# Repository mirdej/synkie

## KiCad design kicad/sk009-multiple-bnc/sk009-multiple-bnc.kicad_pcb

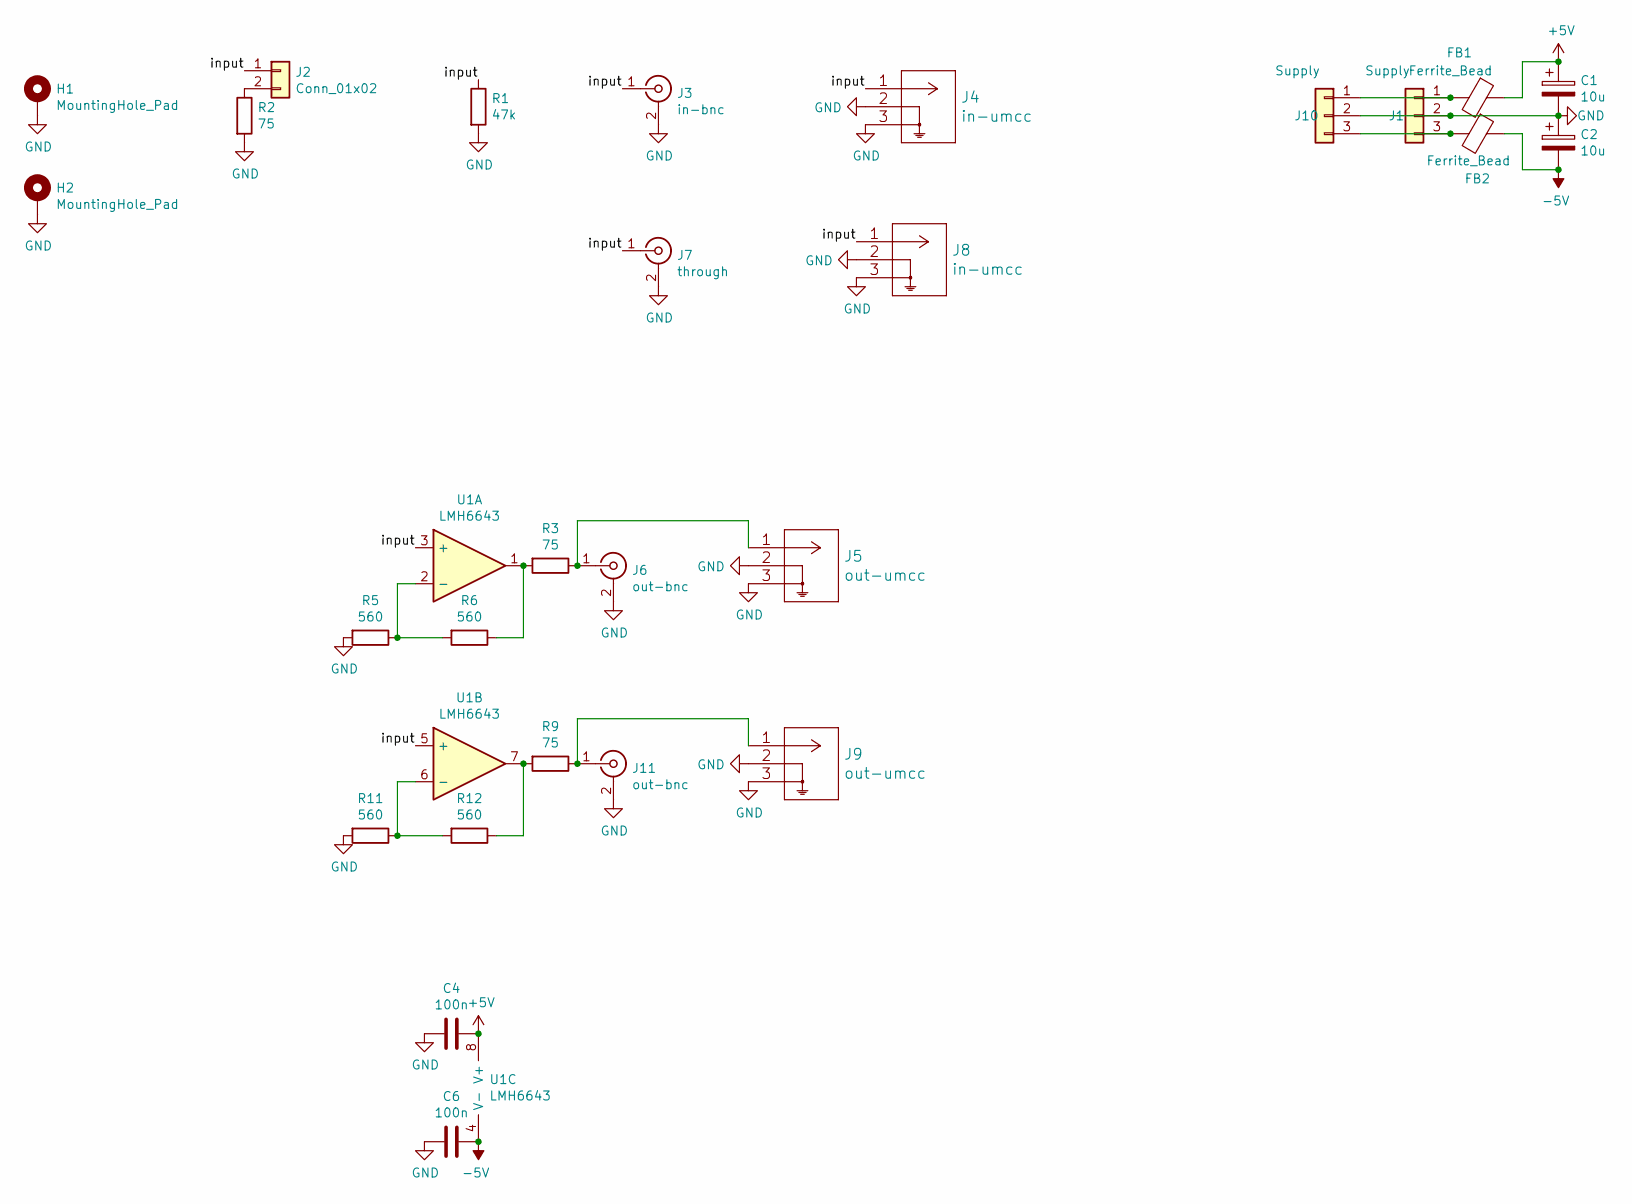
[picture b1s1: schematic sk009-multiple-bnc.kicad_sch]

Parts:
C1, C2: 10u; C_0805_2012Metric; LCSC C15850
C4, C6: 100n; C_0603_1608Metric; LCSC C14663
FB1, FB2: Ferrite_Bead; L_0805_2012Metric; LCSC C1017
H1, H2: MountingHole_Pad; MountingHole_3.2mm_M3_DIN965_Pad
J1, J10: Supply; Molex_KK-254_AE-6410-03A_1x03_P2.54mm_Vertical
J2: Conn_01x02; PinHeader_1x02_P2.54mm_Vertical
J3: in-bnc; BNC_Aliexpress
J4, J8: in-umcc; TE_UMCC_2337019-1
J5, J9: out-umcc; TE_UMCC_2337019-1
J6, J11: out-bnc; BNC_Aliexpress
J7: through; BNC_Aliexpress
R1: 47k; R_0603_1608Metric; LCSC C25819
R2, R3, R9: 75; R_0603_1608Metric; LCSC C4275
R5, R6, R11, R12: 560; R_0603_1608Metric; LCSC C23204
U1: LMH6643; VSSOP-8_3x3mm_P0.65mm; LCSC C478382

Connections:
+5V: C1.1, C4.1, FB1.1, U1.8 (V+)
-5V: C2.2, C6.1, FB2.1, U1.4 (V-)
/input: J2.1, J3.1 (In), J4.1, J7.1 (In), J8.1, R1.1, U1.3 (+), U1.5 (+)
GND: C1.2, C2.1, C4.2, C6.2, H1.1 (1_1), H2.1 (1_1), J1.2, J3.2 (Ext), J4.2, J4.3, J5.2, J5.3, J6.2 (Ext), J7.2 (Ext), J8.2, J8.3, J9.2, J9.3, J10.2, J11.2 (Ext), R1.2, R2.2, R5.2, R11.2
unnamed: FB1.2, J1.1, J10.1
unnamed: FB2.2, J1.3, J10.3
unnamed: J2.2, R2.1
unnamed: J5.1, J6.1 (In), R3.1
unnamed: J9.1, J11.1 (In), R9.1
unnamed: R3.2, R6.1, U1.1
unnamed: R9.2, R12.1, U1.7
unnamed: R5.1, R6.2, U1.2 (-)
unnamed: R11.1, R12.2, U1.6 (-)

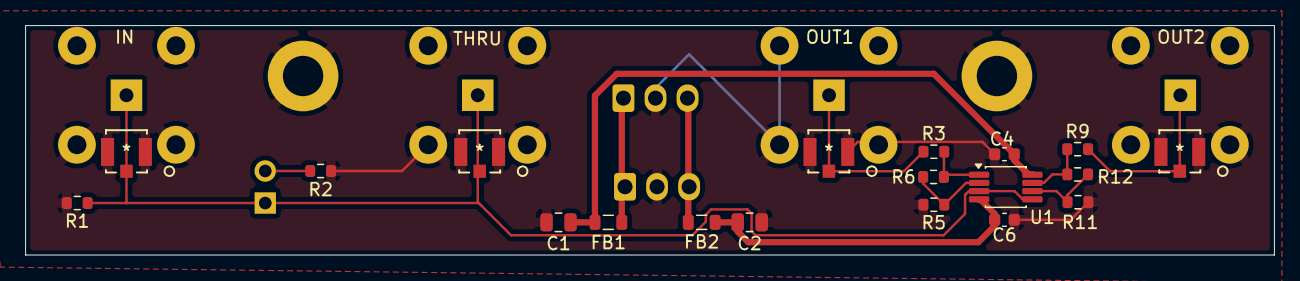
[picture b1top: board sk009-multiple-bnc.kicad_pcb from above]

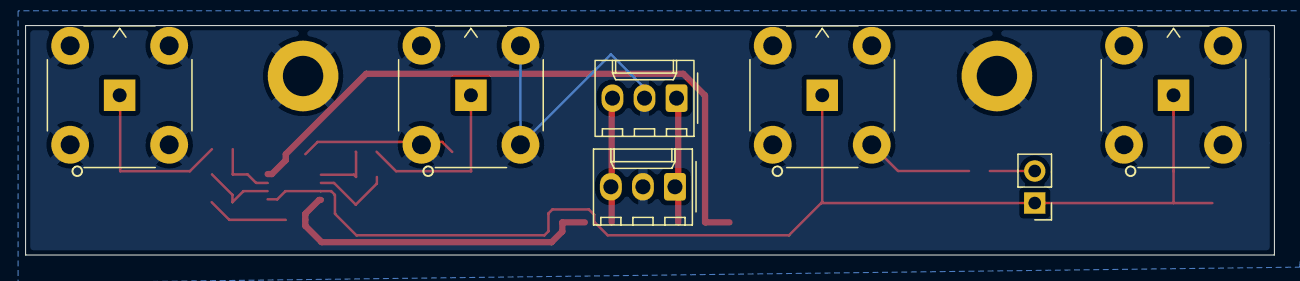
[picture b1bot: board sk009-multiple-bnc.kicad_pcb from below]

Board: 2 copper layers, 99.0 x 18.2 mm, 28 parts (7 on the bottom side), 13 nets.

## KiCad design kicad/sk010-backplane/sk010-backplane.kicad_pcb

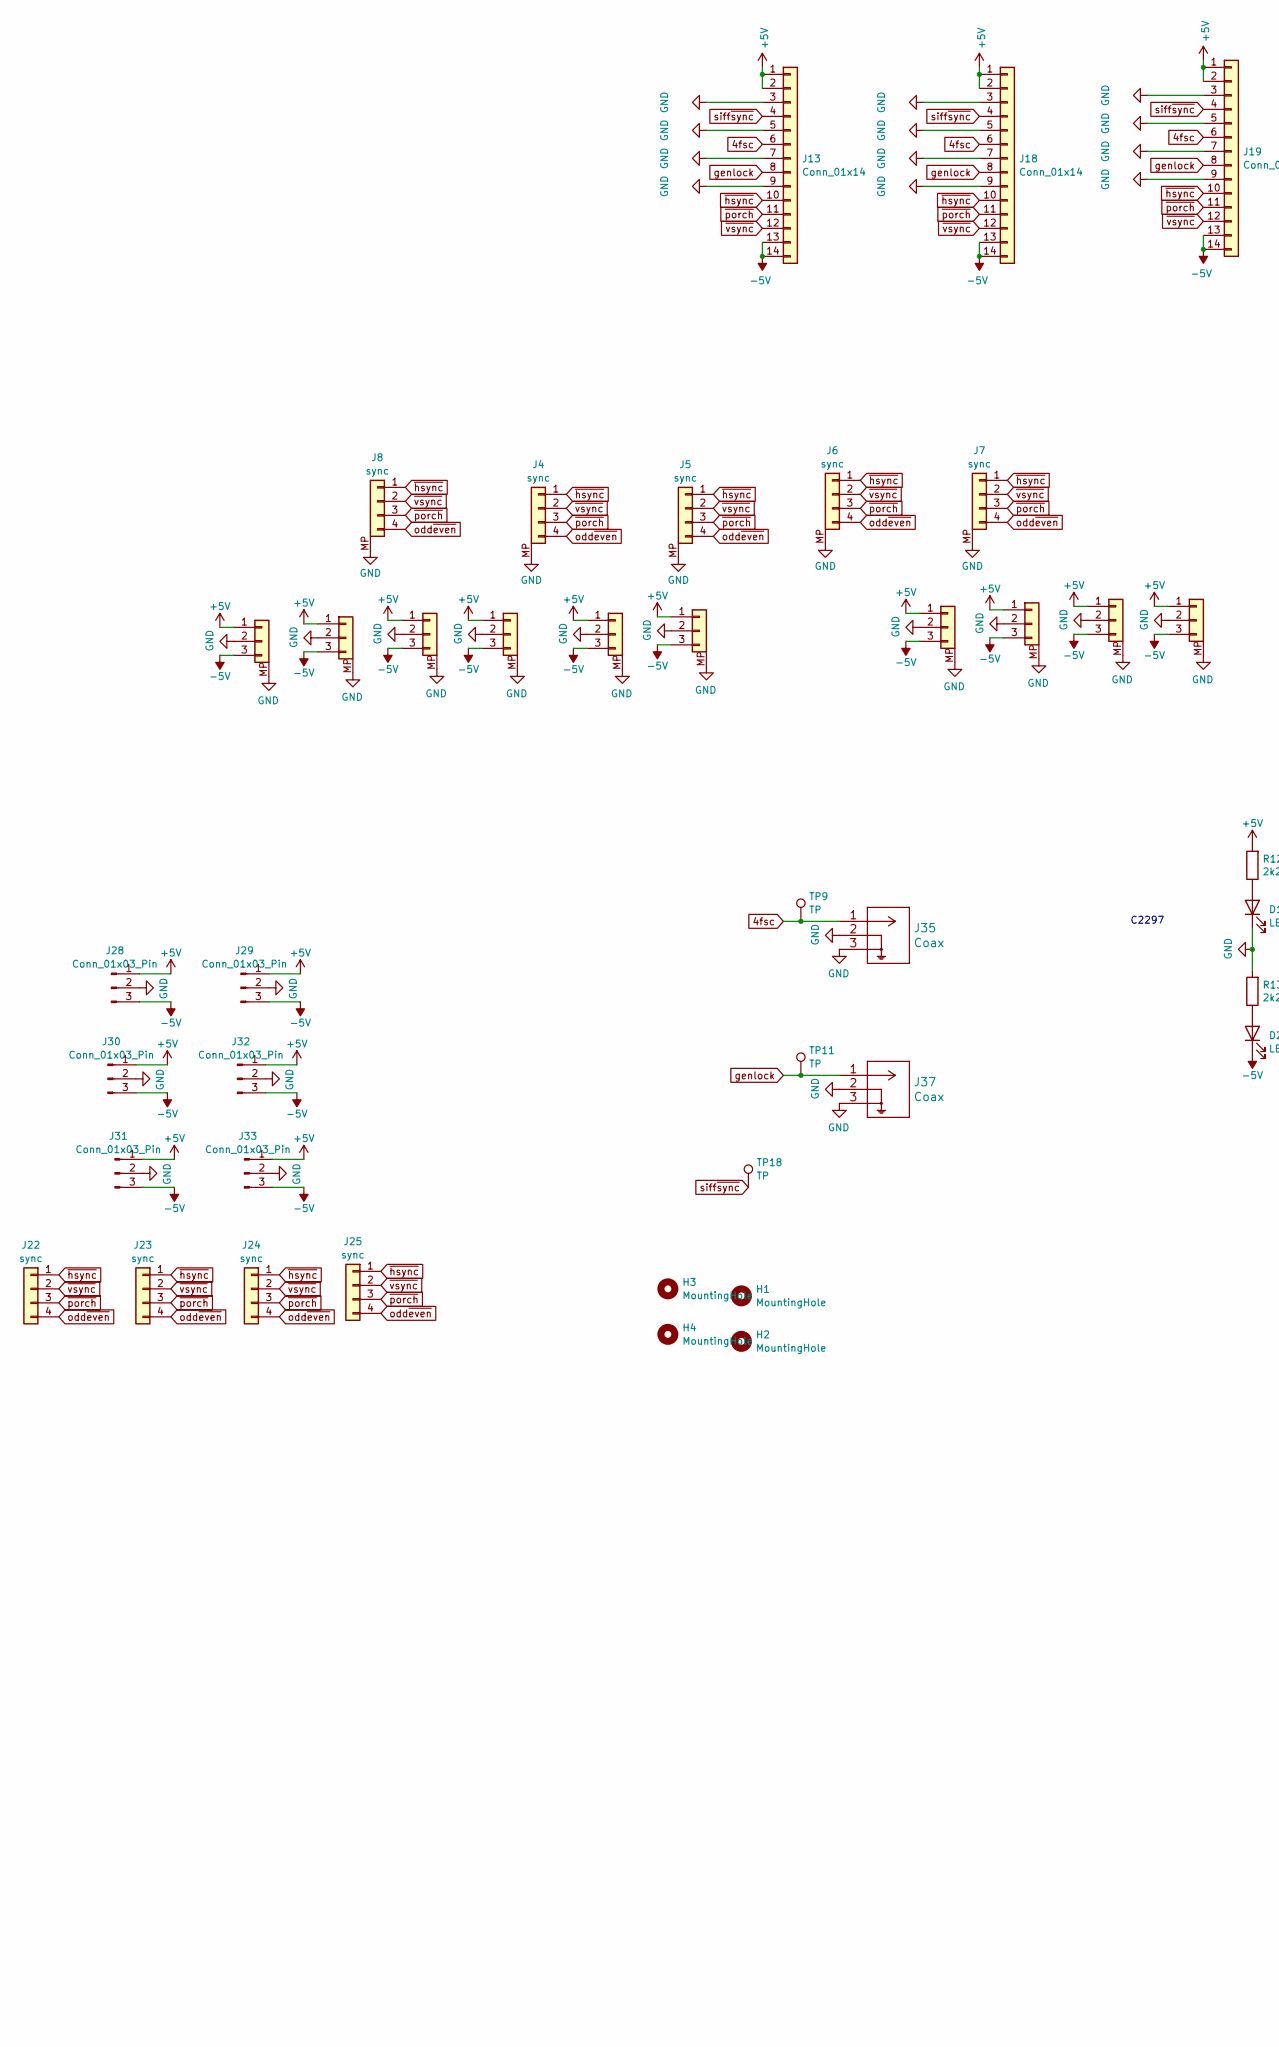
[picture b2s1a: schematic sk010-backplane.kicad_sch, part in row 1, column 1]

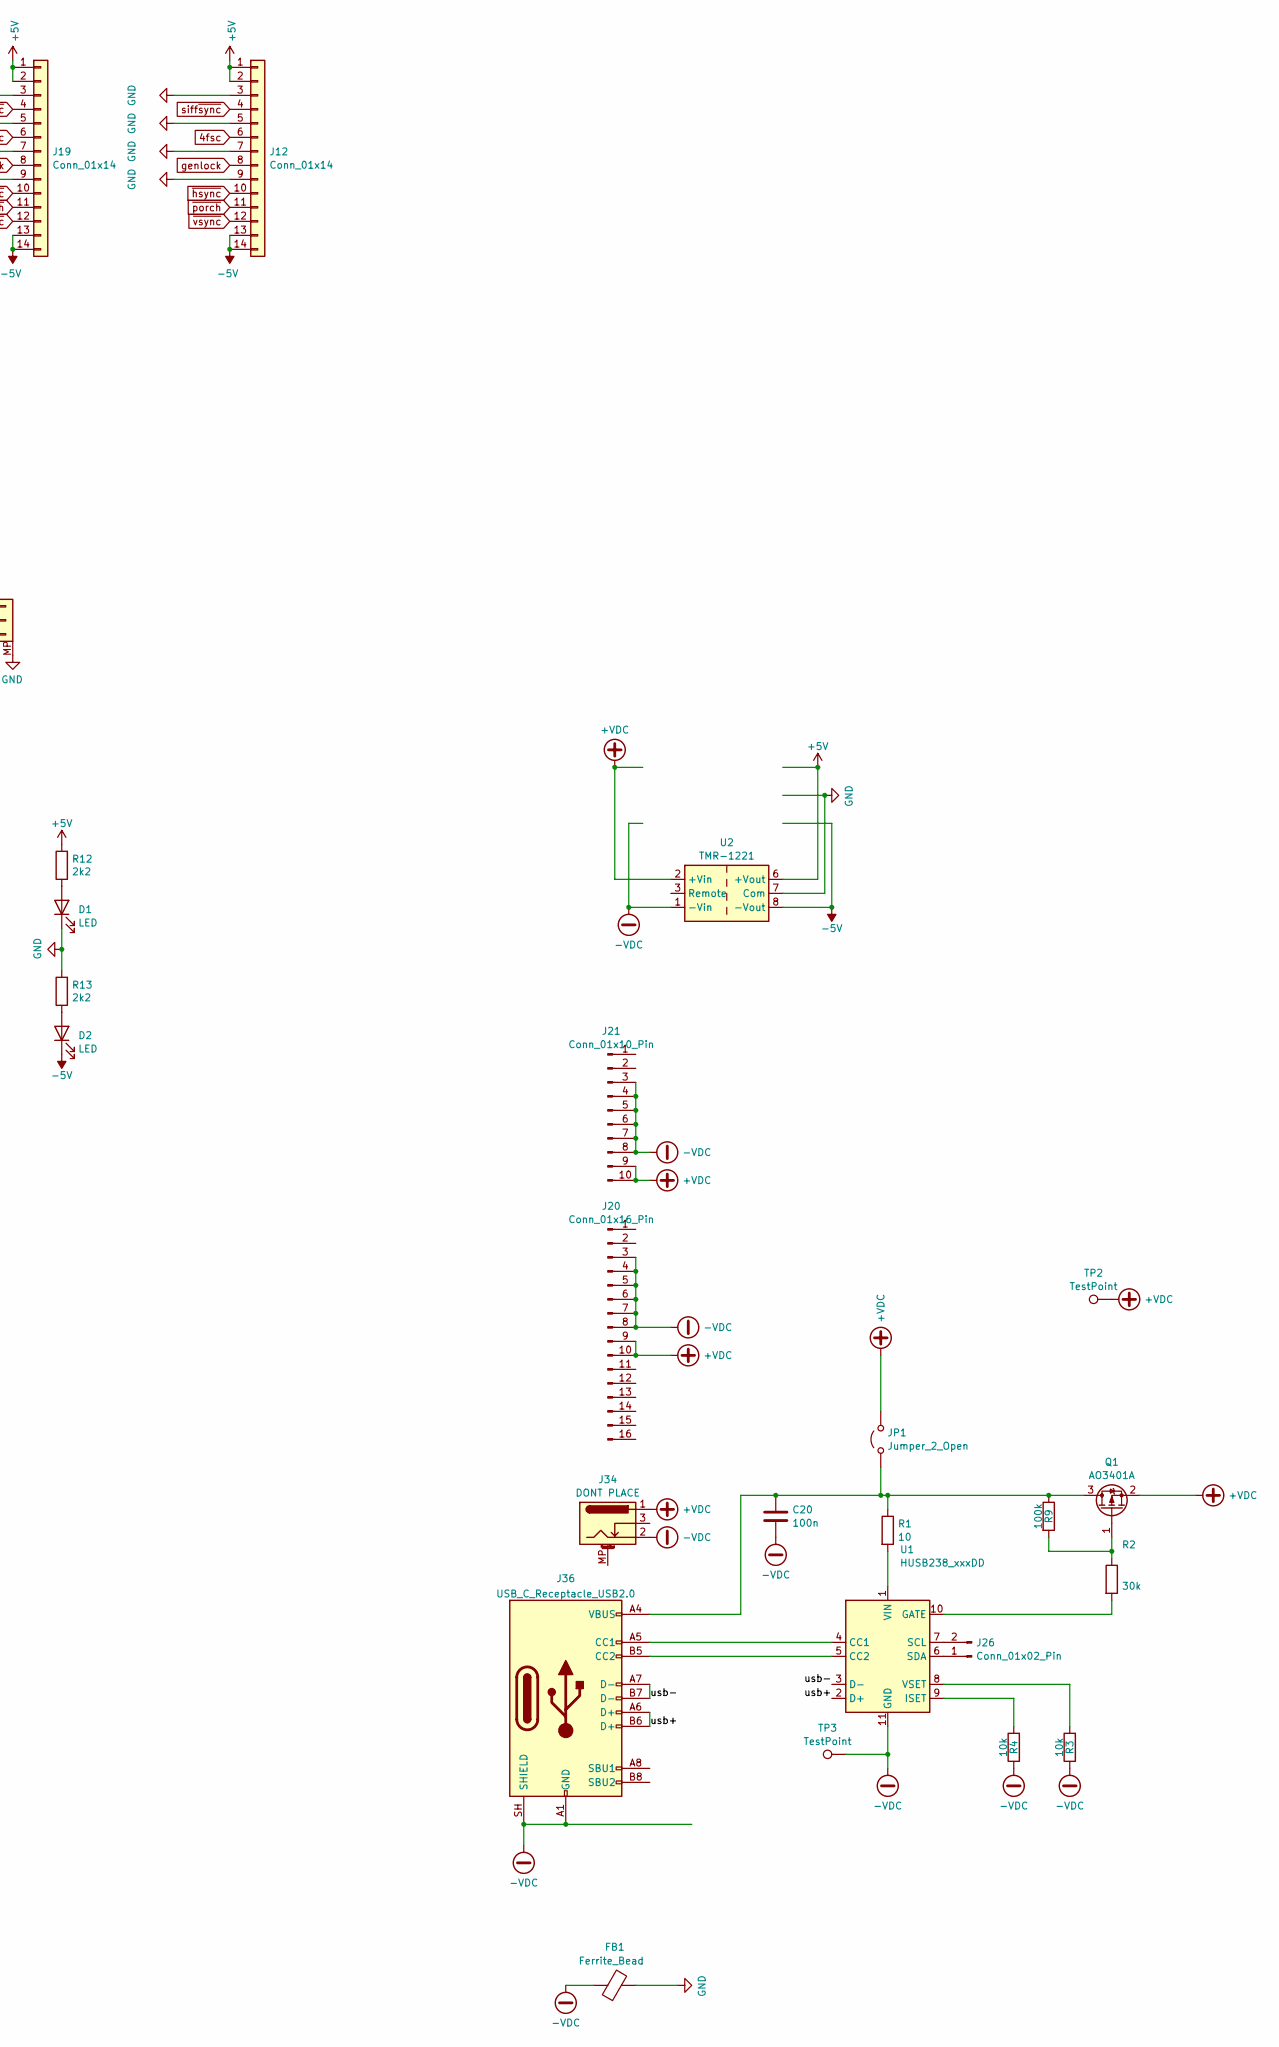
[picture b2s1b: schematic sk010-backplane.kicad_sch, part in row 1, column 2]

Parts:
C20: 100n; C_0603_1608Metric; LCSC C14663
D1, D2: LED; LED_0805_2012Metric; LCSC C2297
FB1: Ferrite_Bead; L_0805_2012Metric_Pad1.15x1.40mm_HandSolder; LCSC C1017
H1, H2, H3, H4: MountingHole; MountingHole_3.2mm_M3_DIN965
J1, J2, J3, J9, J10, J11, J14, J15, J16, J17: Conn_01x03; Molex_PicoBlade_53398-0371_1x03-1MP_P1.25mm_Vertical; LCSC C293633
J4, J5, J6, J7, J8: sync; Molex_PicoBlade_53398-0471_1x04-1MP_P1.25mm_Vertical
J12, J13, J18, J19: Conn_01x14; IDC-Header_2x07_P2.54mm_Vertical
J20: Conn_01x16_Pin; IDC-Header_2x08_P2.54mm_Vertical
J21: Conn_01x10_Pin; IDC-Header_2x05_P2.54mm_Vertical
J22, J23, J24, J25: sync; Molex_KK-254_AE-6410-04A_1x04_P2.54mm_Vertical; LCSC C17617036
J26: Conn_01x02_Pin; smd-2pin
J28, J29, J30, J31, J32, J33: Conn_01x03_Pin; Molex_KK-254_AE-6410-03A_1x03_P2.54mm_Vertical
J34: DONT PLACE; BarrelJack_CUI_PJ-079BH_Horizontal
J35, J37: Coax; TE_UMCC_2337019-1; LCSC C5137195
J36: USB_C_Receptacle_USB2.0; USB_C_Receptacle_HRO_TYPE-C-31-M-12; LCSC C165948
JP1: Jumper_2_Open; SolderJumper-2_P1.3mm_Open_Pad1.0x1.5mm
Q1: AO3401A; SOT-23; LCSC C15127
R1: 10; R_0603_1608Metric; LCSC C22859
R2: 30k; R_0603_1608Metric; LCSC C22984
R3, R4: 10k; R_0603_1608Metric; LCSC C25804
R9: 100k; R_0603_1608Metric; LCSC C25803
R12, R13: 2k2; R_0603_1608Metric; LCSC C4190
TP2, TP3: TestPoint; TestPoint_THTPad_D4.0mm_Drill2.0mm
TP9, TP11, TP18: TP; TestPoint_THTPad_D4.0mm_Drill2.0mm
U1: HUSB238_xxxDD; WDFN-10-1EP_3x3mm_P0.5mm_EP1.8x2.5mm; LCSC C7471904
U2: TMR-1221; Converter_DCDC_TRACO_TEC2-12xxWI_24xxWI_48xxWI_THT

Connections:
4fsc: J12.6, J13.6, J18.6, J19.6, J35.1, TP9.1 (1_1)
+5V: J1.1, J2.1, J3.1, J9.1, J10.1, J11.1, J12.1, J12.2, J13.1, J13.2, J14.1, J15.1, J16.1, J17.1, J18.1, J18.2, J19.1, J19.2, J28.1, J29.1, J30.1, J31.1, J32.1, J33.1, R12.2, U2.6 (+Vout)
+VDC: J20.9, J20.10, J21.9, J21.10, J34.1, JP1.2 (B), Q1.2 (S), TP2.1 (1_1), U2.2 (+Vin)
-5V: D2.1 (K), J1.3, J2.3, J3.3, J9.3, J10.3, J11.3, J12.13, J12.14, J13.13, J13.14, J14.3, J15.3, J16.3, J17.3, J18.13, J18.14, J19.13, J19.14, J28.3, J29.3, J30.3, J31.3, J32.3, J33.3, U2.8 (-Vout)
-VDC: C20.1, FB1.1, J20.3, J20.4, J20.5, J20.6, J20.7, J20.8, J21.3, J21.4, J21.5, J21.6, J21.7, J21.8, J34.2, J36.A1 (GND), J36.A12 (GND), J36.B1 (GND), J36.B12 (GND), J36.SH (SHIELD), R3.1, R4.1, TP3.1 (1_1), U1.11 (GND), U2.1 (-Vin)
/usb+: J36.A6 (D+), J36.B6 (D+), U1.2 (D+)
/usb-: J36.A7 (D-), J36.B7 (D-), U1.3 (D-)
GND: D1.1 (K), FB1.2, J1.2, J1.MP, J2.2, J2.MP, J3.2, J3.MP, J4.MP, J5.MP, J6.MP, J7.MP, J8.MP, J9.2, J9.MP, J10.2, J10.MP, J11.2, J11.MP, J12.3, J12.5, J12.7, J12.9, J13.3, J13.5, J13.7, J13.9, J14.2, J14.MP, J15.2, J15.MP, J16.2, J16.MP, J17.2, J17.MP, J18.3, J18.5, J18.7, J18.9, J19.3, J19.5, J19.7, J19.9, J28.2, J29.2, J30.2, J31.2, J32.2, J33.2, J35.2, J35.3, J37.2, J37.3, R13.2, U2.7 (Com)
unnamed: D1.2 (A), R12.1
unnamed: D2.2 (A), R13.1
unnamed: J26.1, U1.6 (SDA)
unnamed: J26.2, U1.7 (SCL)
unnamed: J36.A5 (CC1), U1.4 (CC1)
unnamed: J36.B5 (CC2), U1.5 (CC2)
unnamed: C20.2, J36.A4 (VBUS), J36.A9 (VBUS), J36.B4 (VBUS), J36.B9 (VBUS), JP1.1 (A), Q1.3 (D), R1.1, R9.1
unnamed: Q1.1 (G), R2.1, R9.2
unnamed: R2.2, U1.10 (GATE)
unnamed: R4.2, U1.9 (ISET)
unnamed: R1.2, U1.1 (VIN)
unnamed: R3.2, U1.8 (VSET)
genlock: J12.8, J13.8, J18.8, J19.8, J37.1, TP11.1 (1_1)
odd~even: J4.4, J5.4, J6.4, J7.4, J8.4, J22.4, J23.4, J24.4, J25.4
siff~sync: J12.4, J13.4, J18.4, J19.4, TP18.1 (1_1)
~hsync: J4.1, J5.1, J6.1, J7.1, J8.1, J12.10, J13.10, J18.10, J19.10, J22.1, J23.1, J24.1, J25.1
~porch: J4.3, J5.3, J6.3, J7.3, J8.3, J12.11, J13.11, J18.11, J19.11, J22.3, J23.3, J24.3, J25.3
~vsync: J4.2, J5.2, J6.2, J7.2, J8.2, J12.12, J13.12, J18.12, J19.12, J22.2, J23.2, J24.2, J25.2

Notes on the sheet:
C2297

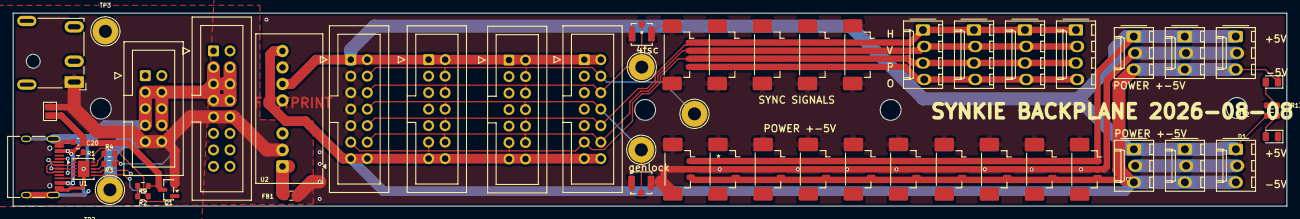
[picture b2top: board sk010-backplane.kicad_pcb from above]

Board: 2 copper layers, 196.1 x 29.7 mm, 60 parts (1 on the bottom side), 26 nets.

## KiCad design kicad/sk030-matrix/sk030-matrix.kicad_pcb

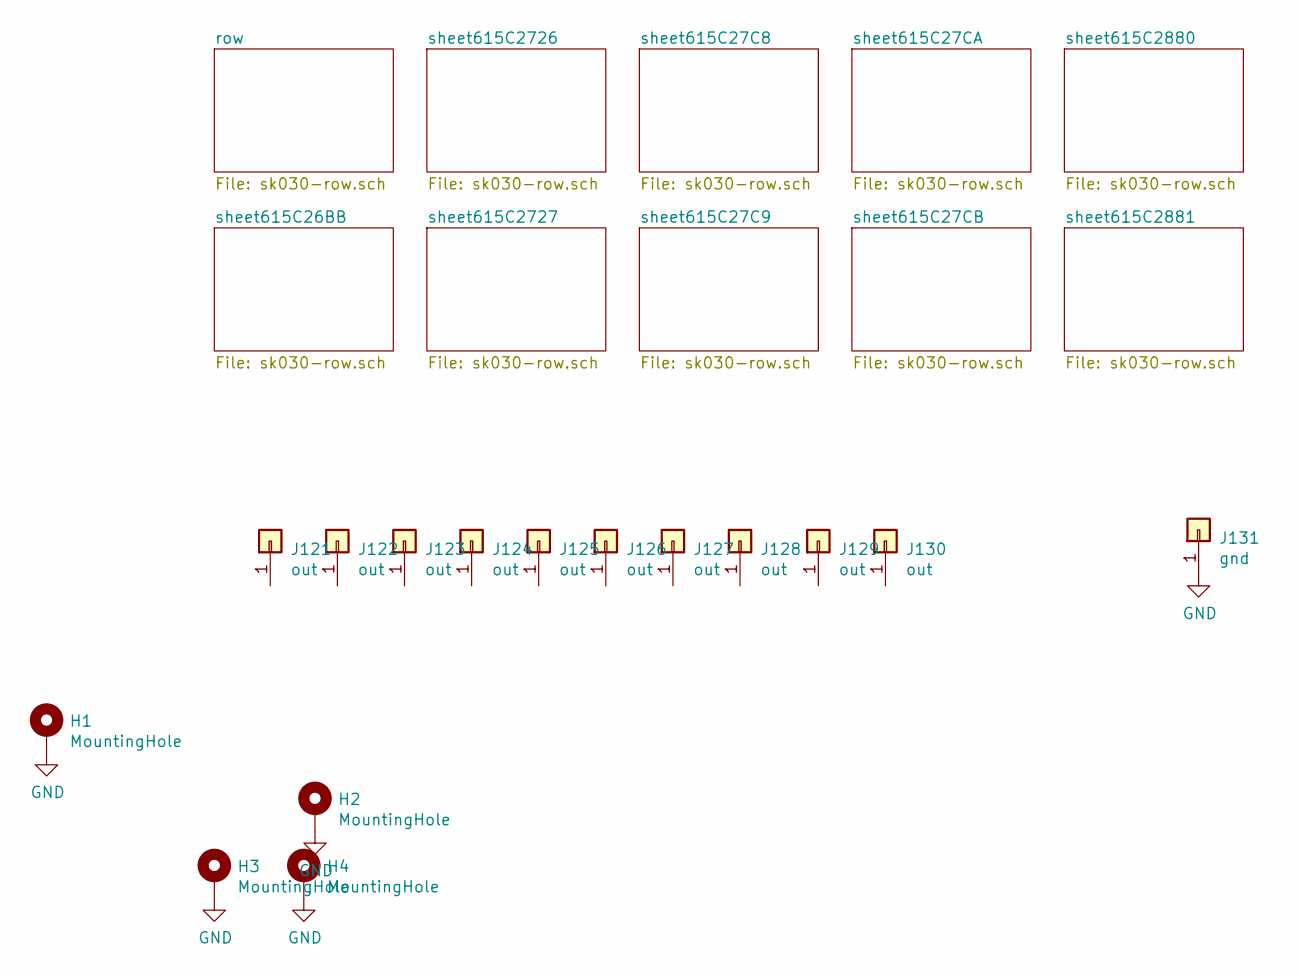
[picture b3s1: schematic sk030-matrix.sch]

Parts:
H1, H2, H3, H4: MountingHole; MountingHole_2.7mm_M2.5
J121, J122, J123, J124, J125, J126, J127, J128, J129, J130: out; Matrixpad
J131: gnd; smd-1pin

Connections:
GND: H1.1, H2.1, H3.1, H4.1, J131.1

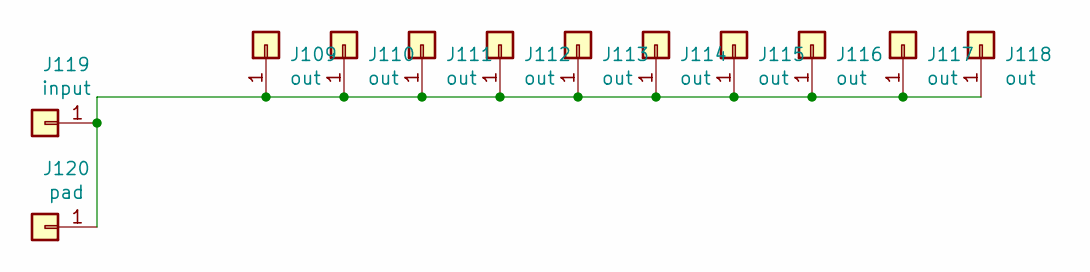
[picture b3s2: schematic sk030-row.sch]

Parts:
J1, J2, J3, J4, J5, J6, J7, J8, J9, J10: out; Matrixpad
J11: input; Matrixpad
J12: pad; smd-1pin

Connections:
unnamed: J1.1, J2.1, J3.1, J4.1, J5.1, J6.1, J7.1, J8.1, J9.1, J10.1, J11.1, J12.1

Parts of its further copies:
J13, J14, J15, J16, J17, J18, J19, J20, J21, J22, J25, J26, J27, J28, J29, J30, J31, J32, J33, J34, J37, J38, J39, J40, J41, J42, J43, J44, J45, J46, J49, J50, J51, J52, J53, J54, J55, J56, J57, J58, J61, J62, J63, J64, J65, J66, J67, J68, J69, J70, J73, J74, J75, J76, J77, J78, J79, J80, J81, J82, J85, J86, J87, J88, J89, J90, J91, J92, J93, J94, J97, J98, J99, J100, J101, J102, J103, J104, J105, J106, J109, J110, J111, J112, J113, J114, J115, J116, J117, J118: out; Matrixpad
J23, J35, J47, J59, J71, J83, J95, J107, J119: input; Matrixpad
J24, J36, J48, J60, J72, J84, J96, J108, J120: pad; smd-1pin

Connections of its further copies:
unnamed: J13.1, J14.1, J15.1, J16.1, J17.1, J18.1, J19.1, J20.1, J21.1, J22.1, J23.1, J24.1
unnamed: J25.1, J26.1, J27.1, J28.1, J29.1, J30.1, J31.1, J32.1, J33.1, J34.1, J35.1, J36.1
unnamed: J37.1, J38.1, J39.1, J40.1, J41.1, J42.1, J43.1, J44.1, J45.1, J46.1, J47.1, J48.1
unnamed: J49.1, J50.1, J51.1, J52.1, J53.1, J54.1, J55.1, J56.1, J57.1, J58.1, J59.1, J60.1
unnamed: J61.1, J62.1, J63.1, J64.1, J65.1, J66.1, J67.1, J68.1, J69.1, J70.1, J71.1, J72.1
unnamed: J73.1, J74.1, J75.1, J76.1, J77.1, J78.1, J79.1, J80.1, J81.1, J82.1, J83.1, J84.1
unnamed: J85.1, J86.1, J87.1, J88.1, J89.1, J90.1, J91.1, J92.1, J93.1, J94.1, J95.1, J96.1
unnamed: J97.1, J98.1, J99.1, J100.1, J101.1, J102.1, J103.1, J104.1, J105.1, J106.1, J107.1, J108.1
unnamed: J109.1, J110.1, J111.1, J112.1, J113.1, J114.1, J115.1, J116.1, J117.1, J118.1, J119.1, J120.1

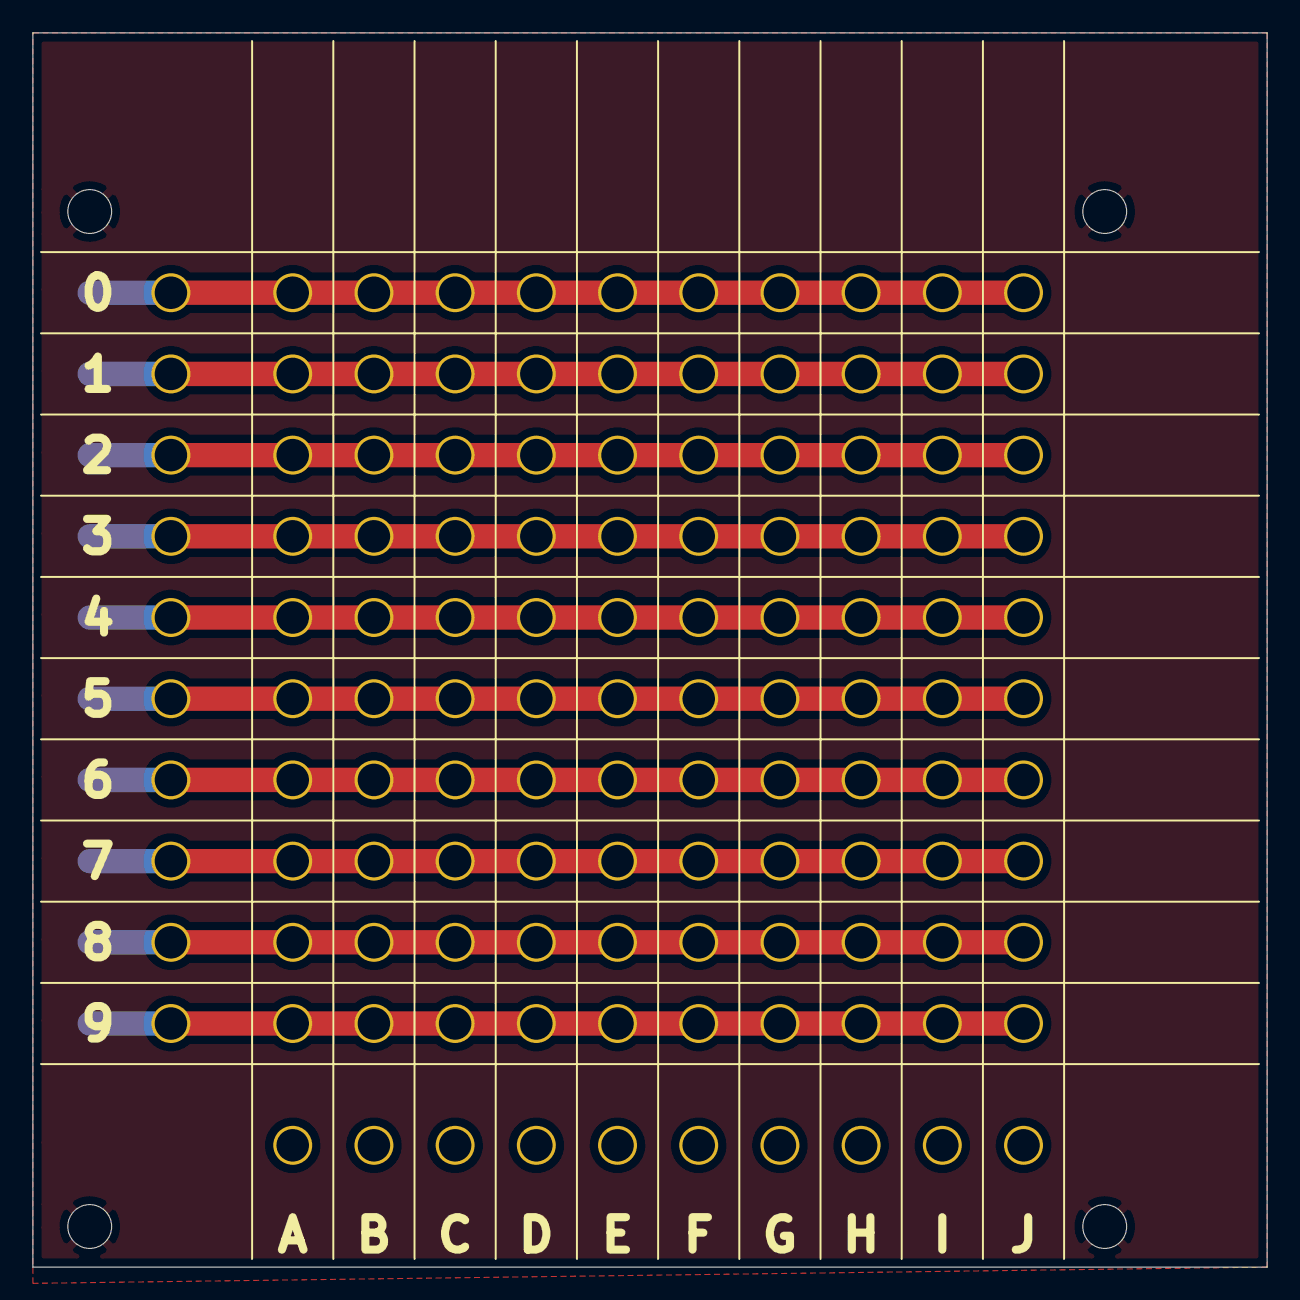
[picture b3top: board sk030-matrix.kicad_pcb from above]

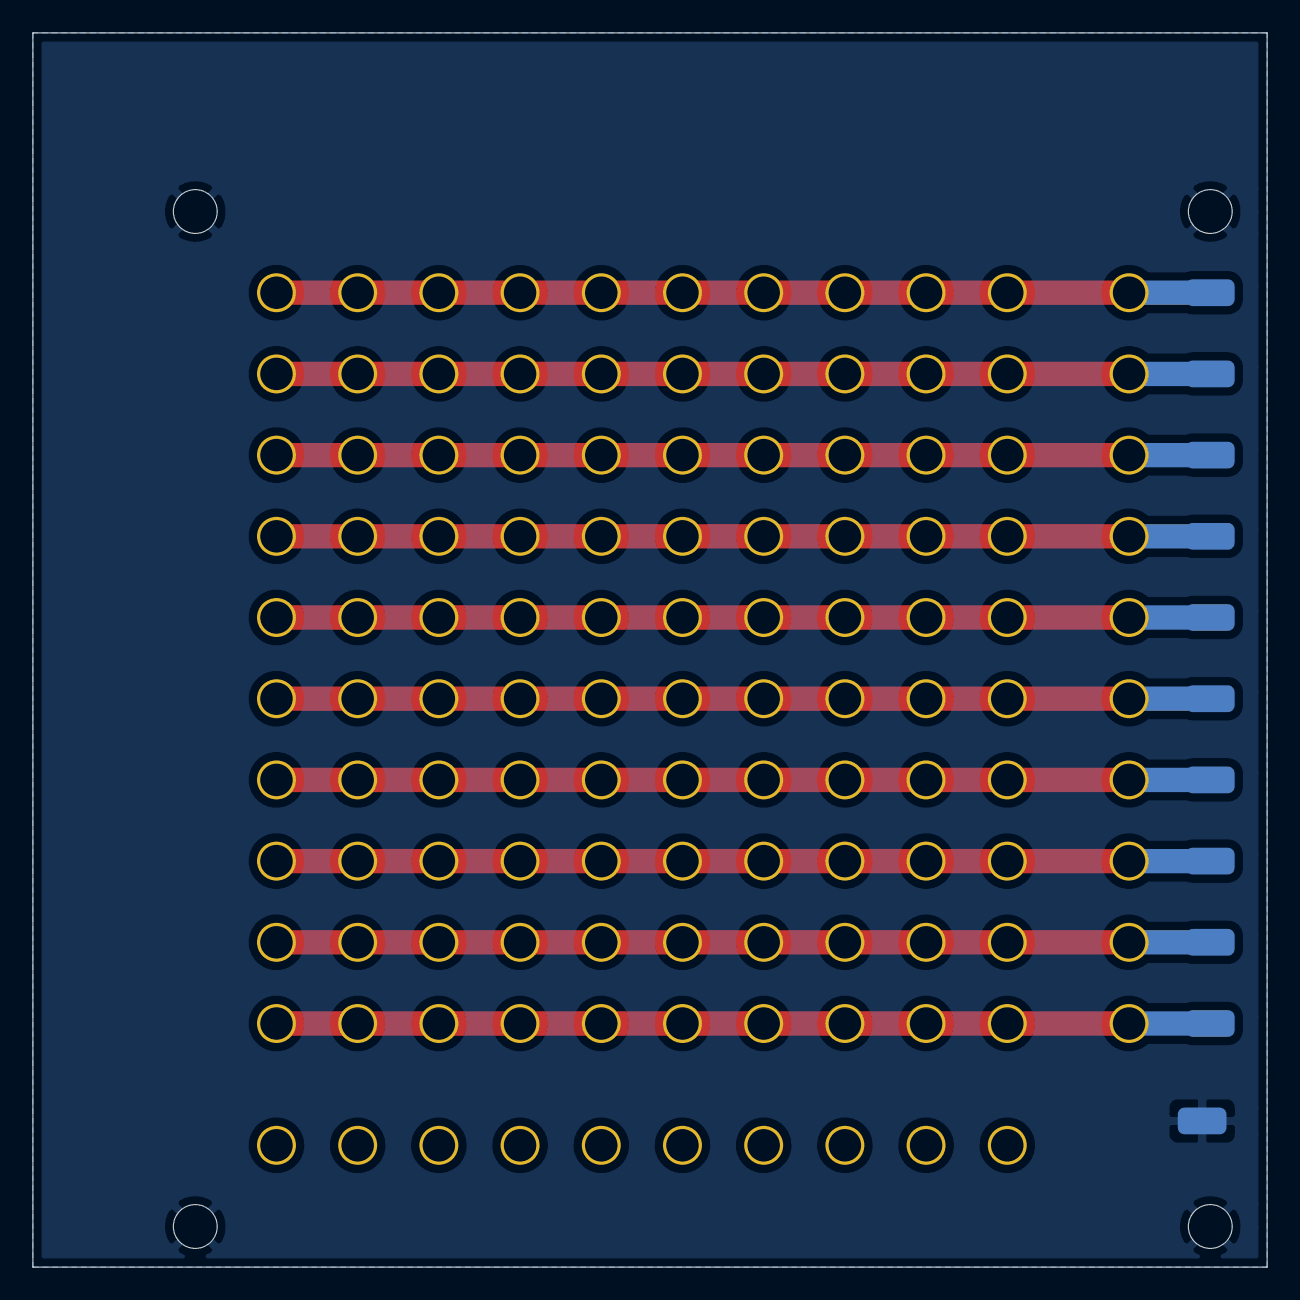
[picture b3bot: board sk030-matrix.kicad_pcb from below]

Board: 2 copper layers, 76.0 x 76.0 mm, 135 parts (11 on the bottom side), 11 nets.

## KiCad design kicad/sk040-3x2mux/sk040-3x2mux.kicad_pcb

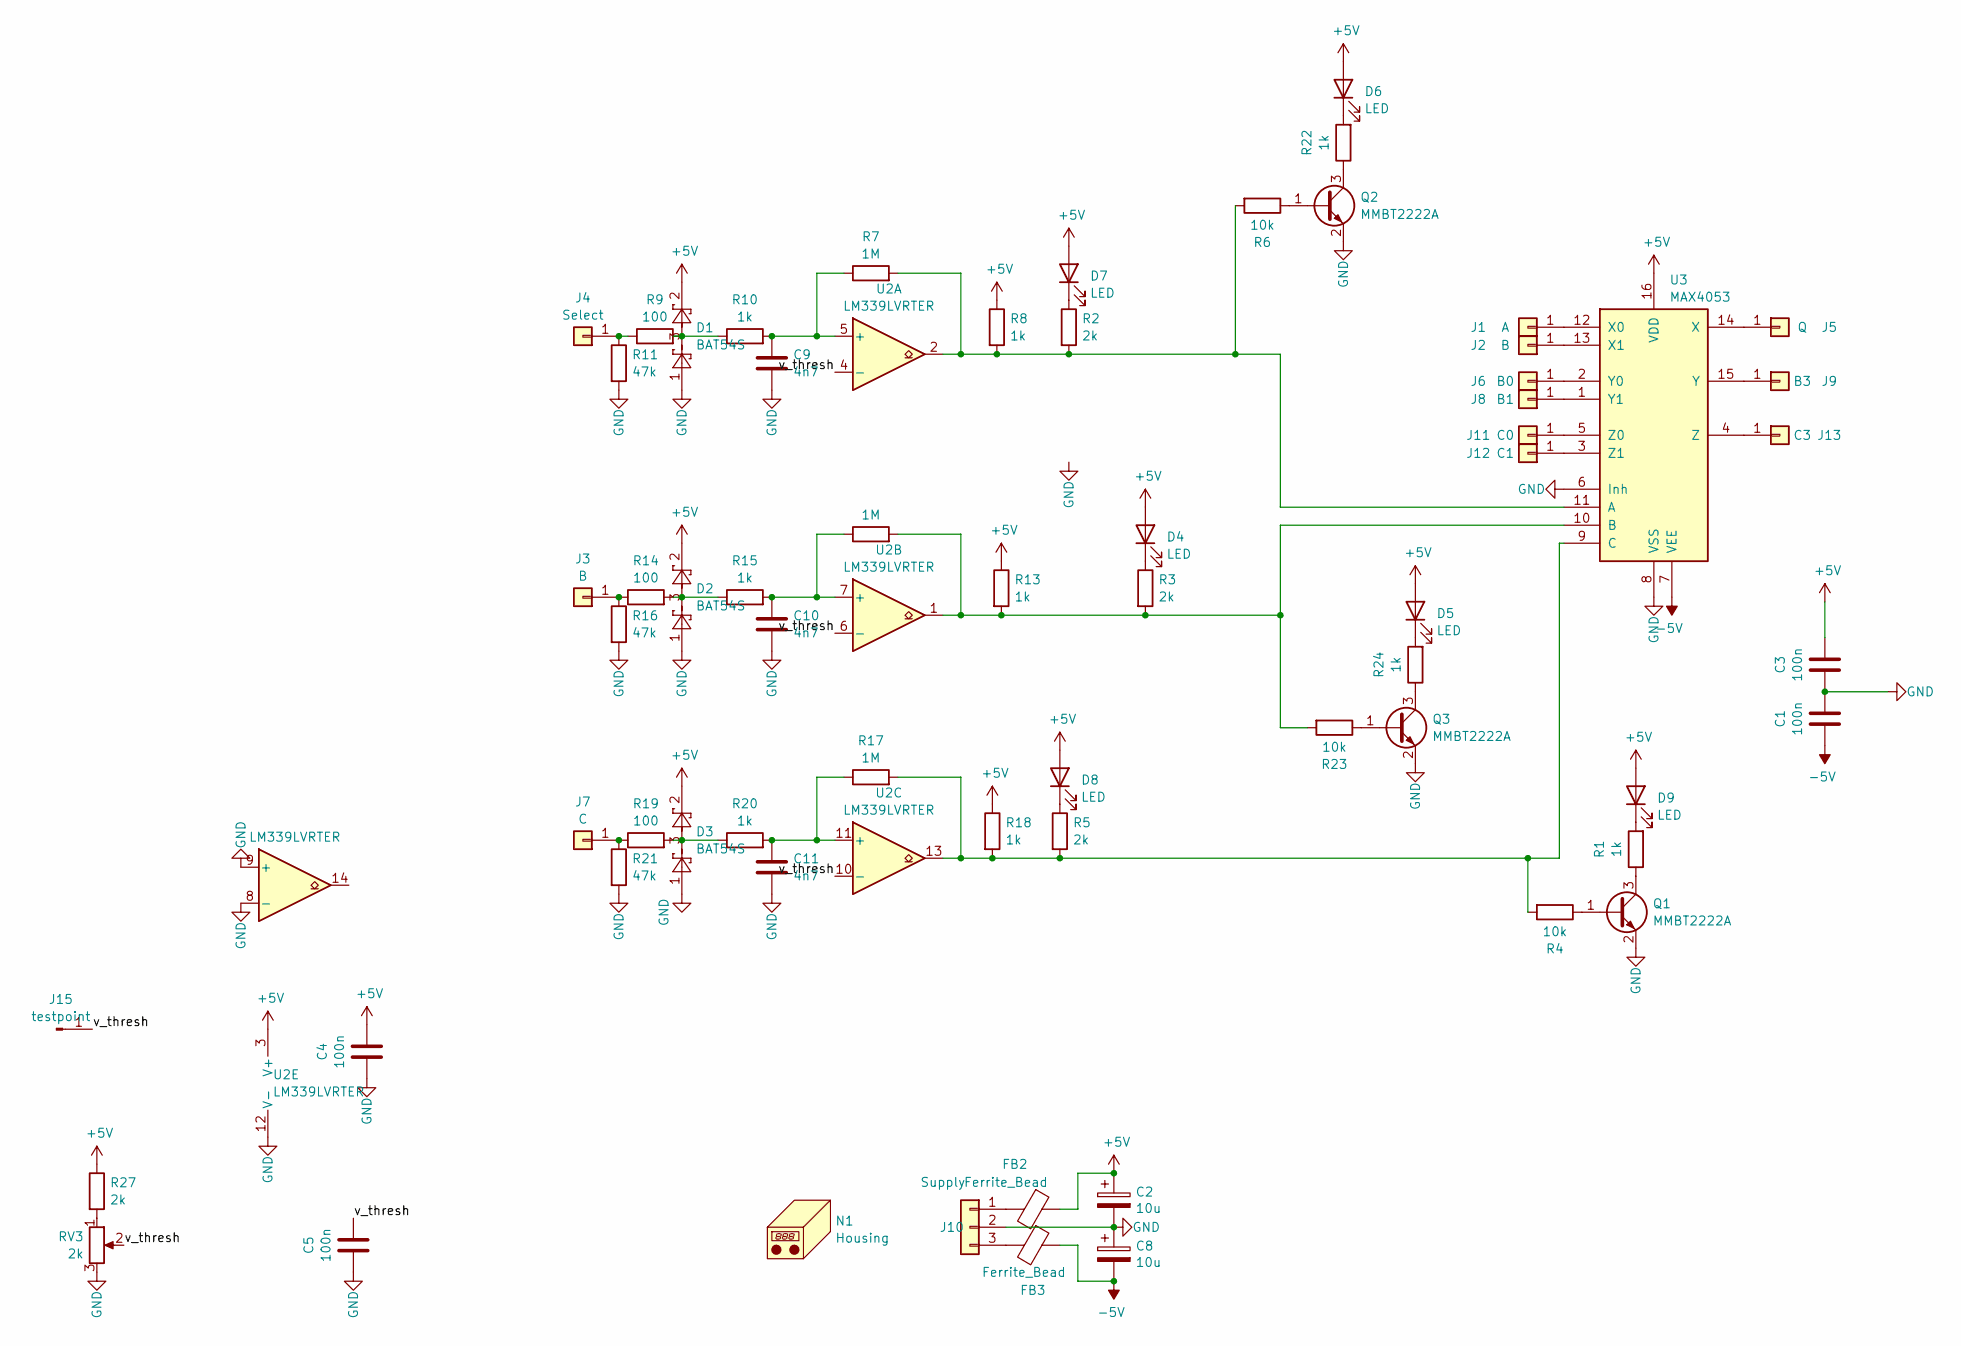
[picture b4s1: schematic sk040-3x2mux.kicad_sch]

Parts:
C1, C3, C4, C5: 100n; R_0603_1608Metric_Pad1.05x0.95mm_HandSolder; LCSC C14663
C2, C8: 10u; C_1206_3216Metric_Pad1.42x1.75mm_HandSolder; LCSC C13585
C9, C10, C11: 4n7; C_0805_2012Metric_Pad1.15x1.40mm_HandSolder; LCSC C1744
D1, D2, D3: BAT54S; SOT-23; LCSC C8592
D4, D5, D6, D7, D8, D9: LED; LED_1206_3216Metric_ReverseMount_Hole1.8x2.4mm; LCSC C125108
FB2, FB3: Ferrite_Bead; L_0805_2012Metric_Pad1.05x1.20mm_HandSolder; LCSC C1017
J1: A; Banana2mm-Löthülse
J2, J3: B; Banana2mm-Löthülse
J4: Select; Banana2mm-Löthülse
J5: Q; Banana2mm-Löthülse
J6: B0; Banana2mm-Löthülse
J7: C; Banana2mm-Löthülse
J8: B1; Banana2mm-Löthülse
J9: B3; Banana2mm-Löthülse
J10: Supply; smd-3pin
J11: C0; Banana2mm-Löthülse
J12: C1; Banana2mm-Löthülse
J13: C3; Banana2mm-Löthülse
J15: testpoint; TestPoint_Pad_D2.0mm
N1: Housing; Frontplate_20mm
Q1, Q2, Q3: MMBT2222A; SOT-23; LCSC C82460
R1, R8, R10, R13, R15, R18, R20, R22, R24: 1k; R_0805_2012Metric_Pad1.15x1.40mm_HandSolder; LCSC C17513
R2, R3, R5, R27: 2k; R_0805_2012Metric_Pad1.15x1.40mm_HandSolder; LCSC C17604
R4, R6, R23: 10k; R_0805_2012Metric_Pad1.15x1.40mm_HandSolder; LCSC C25804
R7, R12, R17: 1M; R_0805_2012Metric_Pad1.15x1.40mm_HandSolder; LCSC C17514
R9, R14, R19: 100; R_0805_2012Metric_Pad1.15x1.40mm_HandSolder; LCSC C17408
R11, R16, R21: 47k; R_0805_2012Metric_Pad1.15x1.40mm_HandSolder; LCSC C17713
RV3: 2k; Potentiometer_Bourns_3224X_Vertical; LCSC C22384649
U2: LM339LVRTER; WQFN-16-1EP_3x3mm_P0.5mm_EP1.6x1.6mm; LCSC C3658606
U3: MAX4053; SOIC-16_3.9x9.9mm_P1.27mm; LCSC C2673376

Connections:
+5V: C2.1, C3.1, C4.1, D1.2, D2.2, D3.2, D4.2 (A), D5.2 (A), D6.2 (A), D7.2 (A), D8.2 (A), D9.2 (A), FB2.1, R8.1, R13.1, R18.1, R27.1, U2.3 (V+), U3.16 (VDD)
-5V: C1.2, C8.2, FB3.1, U3.7 (VEE)
/v_thresh: C5.1, J15.1, RV3.2, U2.4 (-), U2.6 (-), U2.10 (-)
GND: C1.1, C2.2, C3.2, C4.2, C5.2, C8.1, C9.2, C10.2, C11.2, D1.1, D2.1, D3.1, J10.2, Q1.2 (E), Q2.2 (E), Q3.2 (E), R11.2, R16.2, R21.2, RV3.3, U2.8 (-), U2.9 (+), U2.12 (V-), U3.6 (Inh), U3.8 (VSS)
unnamed: D1.3, R9.2, R10.1
unnamed: D2.3, R14.2, R15.1
unnamed: D3.3, R19.2, R20.1
unnamed: D4.1 (K), R3.1
unnamed: D5.1 (K), R24.2
unnamed: D6.1 (K), R22.2
unnamed: D7.1 (K), R2.1
unnamed: D8.1 (K), R5.1
unnamed: D9.1 (K), R1.2
unnamed: J1.1, U3.12 (X0)
unnamed: J2.1, U3.13 (X1)
unnamed: J3.1, R14.1, R16.1
unnamed: J4.1, R9.1, R11.1
unnamed: J5.1, U3.14 (X)
unnamed: J6.1, U3.2 (Y0)
unnamed: J7.1, R19.1, R21.1
unnamed: J8.1, U3.1 (Y1)
unnamed: J9.1, U3.15 (Y)
unnamed: FB2.2, J10.1
unnamed: FB3.2, J10.3
unnamed: J11.1, U3.5 (Z0)
unnamed: J12.1, U3.3 (Z1)
unnamed: J13.1, U3.4 (Z)
unnamed: Q1.1 (B), R4.1
unnamed: Q1.3 (C), R1.1
unnamed: Q2.1 (B), R6.1
unnamed: Q2.3 (C), R22.1
unnamed: Q3.1 (B), R23.1
unnamed: Q3.3 (C), R24.1
unnamed: R27.2, RV3.1
unnamed: C9.1, R7.1, R10.2, U2.5 (+)
unnamed: C10.1, R12.1, R15.2, U2.7 (+)
unnamed: C11.1, R17.1, R20.2, U2.11 (+)
unnamed: R2.2, R6.2, R7.2, R8.2, U2.2, U3.11 (A)
unnamed: R3.2, R12.2, R13.2, R23.2, U2.1, U3.10 (B)
unnamed: R4.2, R5.2, R17.2, R18.2, U2.13, U3.9 (C)

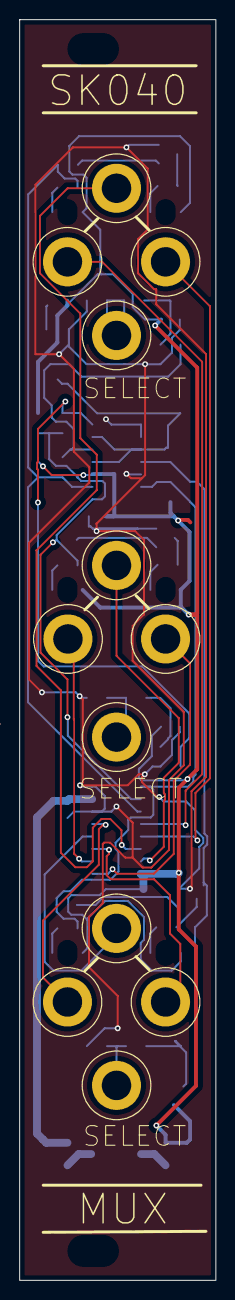
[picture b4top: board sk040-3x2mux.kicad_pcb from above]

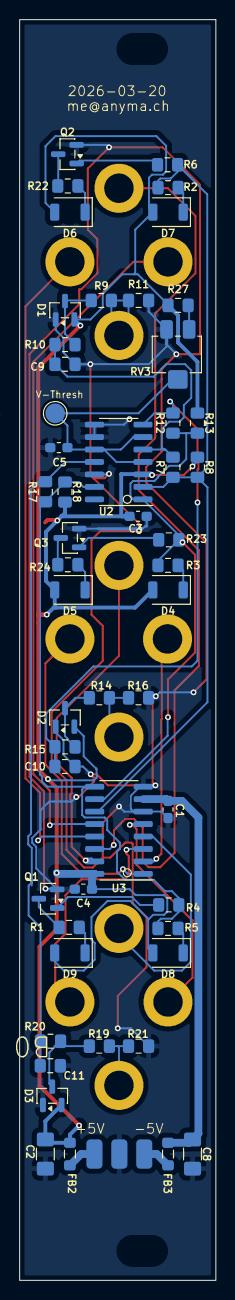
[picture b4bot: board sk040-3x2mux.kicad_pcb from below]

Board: 2 copper layers, 20.0 x 128.5 mm, 66 parts (53 on the bottom side), 40 nets.

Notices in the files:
parts and their libraries:
Copyright 2016 Accelerated Designs. All rights reserved.
